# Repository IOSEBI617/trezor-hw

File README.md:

# Hardware design of TREZOR

https://trezor.io/
IOSEBI

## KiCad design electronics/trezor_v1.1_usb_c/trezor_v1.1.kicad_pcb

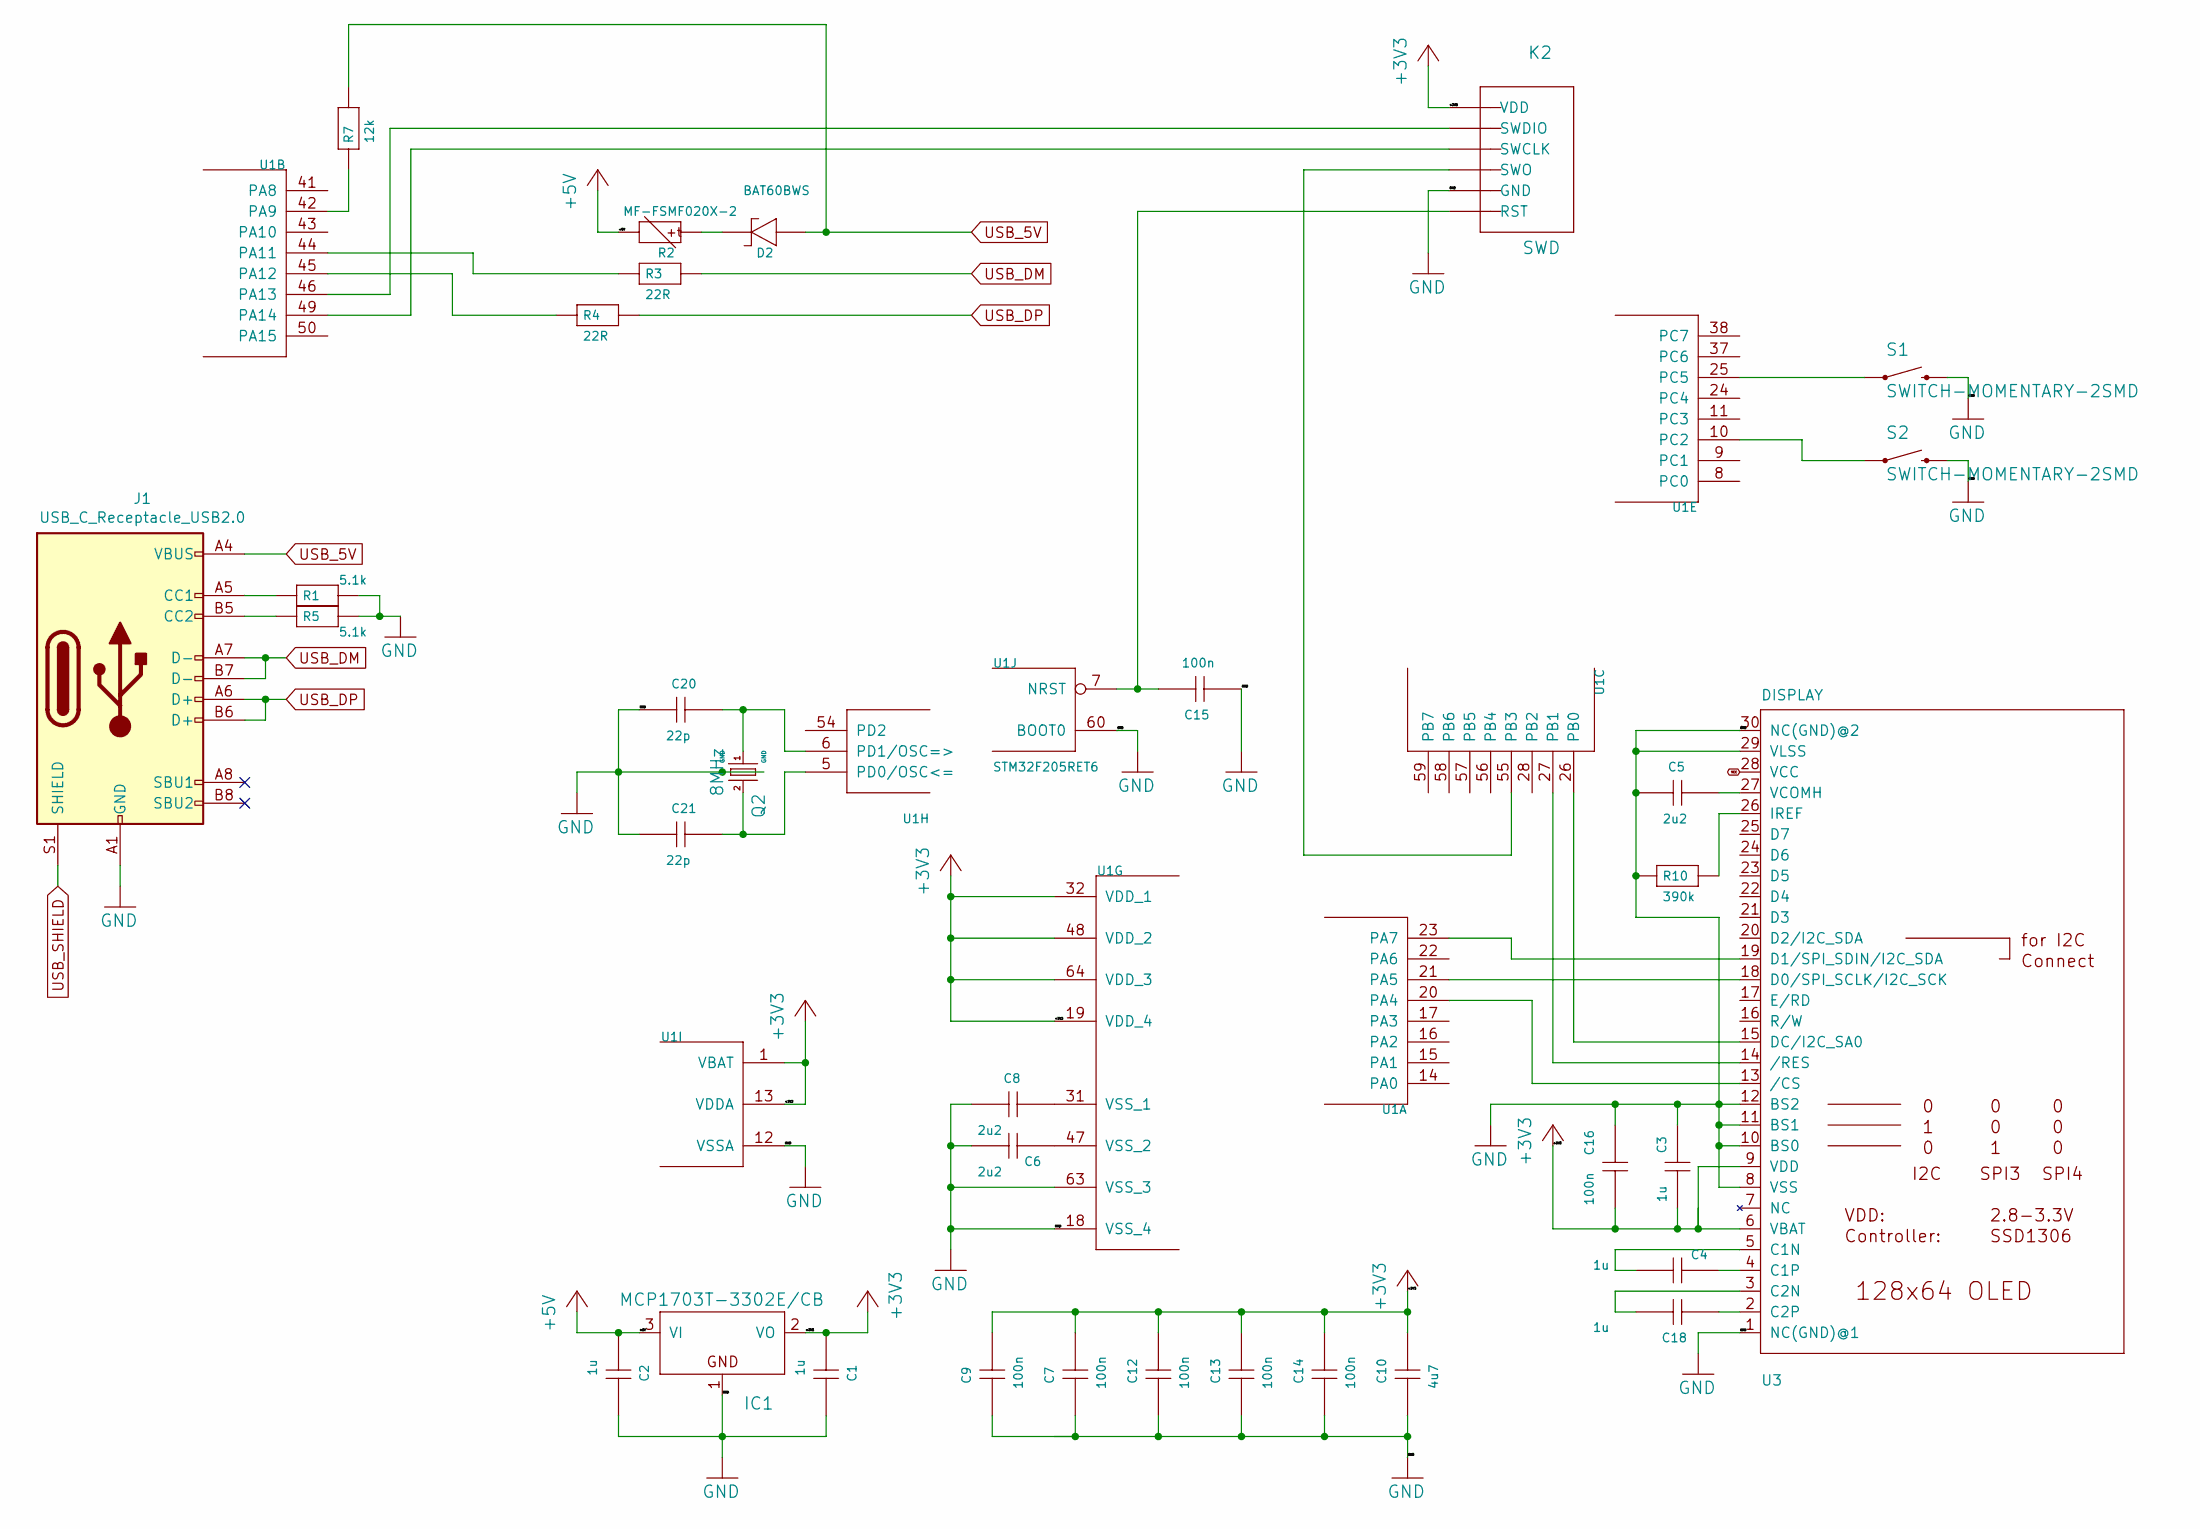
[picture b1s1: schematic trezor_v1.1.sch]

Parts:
C1, C2, C3, C4, C18: 1u; 0402
C5: 2u2; 0603
C6, C8: 2u2; 0402
C7, C9, C12, C13, C14, C15, C16: 100n; 0402
C10: 4u7; 0603
C20, C21: 22p; 0402
D2: BAT60BWS; SOD323
IC1: MCP1703T-3302E/CB; SOT23
J1: USB_C_Receptacle_USB2.0; USB_C_Receptacle_GCT_USB4085
K2: SWD
Q2: 8MHz; CTS406
R1, R5: 5.1k; 0402
R2: MF-FSMF020X-2; 0603
R3, R4: 22R; 0402
R7: 12k; 0402
R10: 390k; 0402
S1, S2: SWITCH-MOMENTARY-2SMD; TACTILE_SWITCH_SMD
U1: STM32F205RET6; TQFP64
U3: DISPLAY; UG-2864HSWEG01_0.96IN_WRAPAROUND

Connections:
+3V3: C1.P$1 (1), C3.P$1 (1), C7.P$2 (2), C9.P$2 (2), C10.2, C12.P$2 (2), C13.P$2 (2), C14.P$2 (2), C16.P$1 (1), IC1.2 (VO), K2.6 (VDD), U1.1 (VBAT), U1.13 (VDDA), U1.19 (VDD_4), U1.32 (VDD_1), U1.48 (VDD_2), U1.64 (VDD_3), U3.6 (VBAT), U3.9 (VDD)
+5V: C2.P$1 (1), IC1.3 (VI), R2.2
GND: C1.P$2 (2), C2.P$2 (2), C3.P$2 (2), C5.1, C6.P$1 (1), C7.P$1 (1), C8.P$1 (1), C9.P$1 (1), C10.1, C12.P$1 (1), C13.P$1 (1), C14.P$1 (1), C15.P$1 (1), C16.P$2 (2), C20.P$1 (1), C21.P$1 (1), IC1.1 (GND), J1.A1 (GND), J1.A12 (GND), J1.B1 (GND), J1.B12 (GND), K2.2 (GND), Q2.2 (GND), Q2.4 (GND), R1.P$2 (2), R5.P$2 (2), R10.P$1 (1), S1.3 (2), S1.4 (2), S2.3 (2), S2.4 (2), U1.12 (VSSA), U1.18 (VSS_4), U1.60 (BOOT0), U1.63 (VSS_3), U3.1 (NC(GND)@1), U3.8 (VSS), U3.10 (BS0), U3.11 (BS1), U3.12 (BS2), U3.29 (VLSS), U3.30 (NC(GND)@2)
unnamed: C4.P$1 (1), U3.4 (C1P)
unnamed: C4.P$2 (2), U3.5 (C1N)
unnamed: C5.2, U3.27 (VCOMH)
unnamed: C6.P$2 (2), U1.47 (VSS_2)
unnamed: C8.P$2 (2), U1.31 (VSS_1)
unnamed: C15.P$2 (2), K2.1 (RST), U1.7 (NRST)
unnamed: C18.P$1 (1), U3.2 (C2P)
unnamed: C18.P$2 (2), U3.3 (C2N)
unnamed: C20.P$2 (2), Q2.1, U1.6 (PD1/OSC=>)
unnamed: C21.P$2 (2), Q2.3 (2), U1.5 (PD0/OSC<=)
unnamed: D2.K (2), R2.1
unnamed: J1.A5 (CC1), R1.P$1 (1)
unnamed: J1.B5 (CC2), R5.P$1 (1)
unnamed: K2.3 (SWO), U1.55 (PB3)
unnamed: K2.4 (SWCLK), U1.49 (PA14)
unnamed: K2.5 (SWDIO), U1.46 (PA13)
unnamed: R3.P$1 (1), U1.44 (PA11)
unnamed: R4.P$1 (1), U1.45 (PA12)
unnamed: R7.P$1 (1), U1.42 (PA9)
unnamed: R10.P$2 (2), U3.26 (IREF)
unnamed: S1.1, S1.2 (1), U1.25 (PC5)
unnamed: S2.1, S2.2 (1), U1.10 (PC2)
unnamed: U1.20 (PA4), U3.13 (/CS)
unnamed: U1.21 (PA5), U3.18 (D0/SPI_SCLK/I2C_SCK)
unnamed: U1.23 (PA7), U3.19 (D1/SPI_SDIN/I2C_SDA)
unnamed: U1.26 (PB0), U3.15 (DC/I2C_SA0)
unnamed: U1.27 (PB1), U3.14 (/RES)
USB_5V: D2.A (1), J1.A4 (VBUS), J1.A9 (VBUS), J1.B4 (VBUS), J1.B9 (VBUS), R7.P$2 (2)
USB_DM: J1.A7 (D-), J1.B7 (D-), R3.P$2 (2)
USB_DP: J1.A6 (D+), J1.B6 (D+), R4.P$2 (2)
USB_SHIELD: J1.S1 (SHIELD)
VCC: U3.28 (VCC)

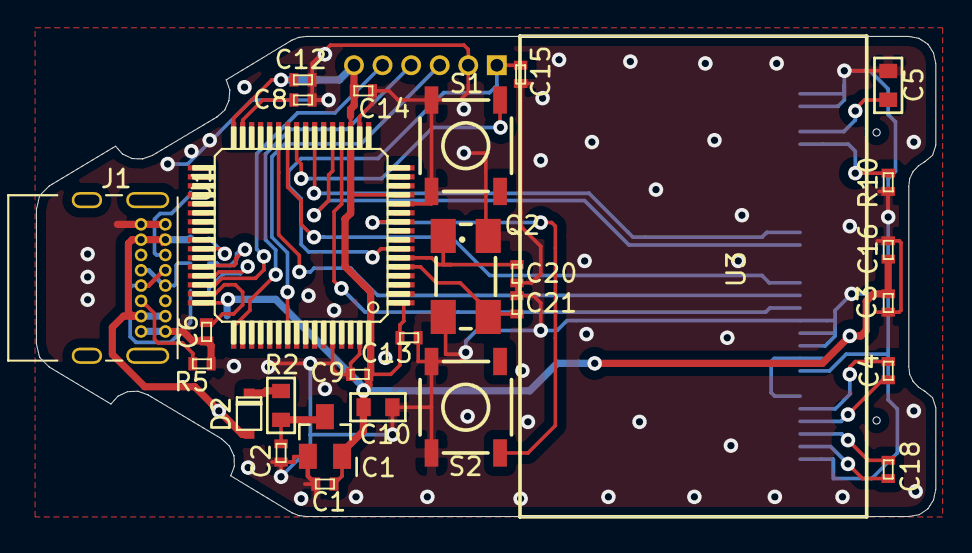
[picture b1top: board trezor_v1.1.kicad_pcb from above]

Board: 2 copper layers, 50.0 x 26.7 mm, 34 parts (0 on the bottom side), 33 nets.

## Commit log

2020-07-12 Add USB-C version of Trezor One
2020-07-12 Fix silkscreen text
2020-07-12 Minor silkscreen fixes, add specifier for JLC order number
2020-07-13 Fix solder mask on all footprints, minor trace cleanup
2020-07-13 Minor silkscreen fixes
2020-08-25 Add 3D models to kicad pcb
2020-08-25 Fix display 3d model location
2020-08-25 Add case CAD files and STLs
2020-09-01 Add STEP recreations of v3 housing
2020-09-01 Create case using v3 files
